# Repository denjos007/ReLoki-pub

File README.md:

# ReLoki-pub

ReLoki  is a Infrastructre-free UWB based relative localization system. It uses a combination of TWR and Geometric AoA for full 3D localizattion and message transfer between participating agents. 

This repository will contain the hardware schematics to get ReLoki operational. 

# Hardware

The files to fabricate the PCB for ReLoki are in hardware folder.
1. ReLoki_ECAD: ReLoki Controller PCB 
2. UWB_Antenna_Circular: Individual circular antenna
3. UWB_Antenna_SqArray: UWB antenna in the uniform circular array configuration
4. 3D Parts: 3D printed parts for the RTA Antenna array.

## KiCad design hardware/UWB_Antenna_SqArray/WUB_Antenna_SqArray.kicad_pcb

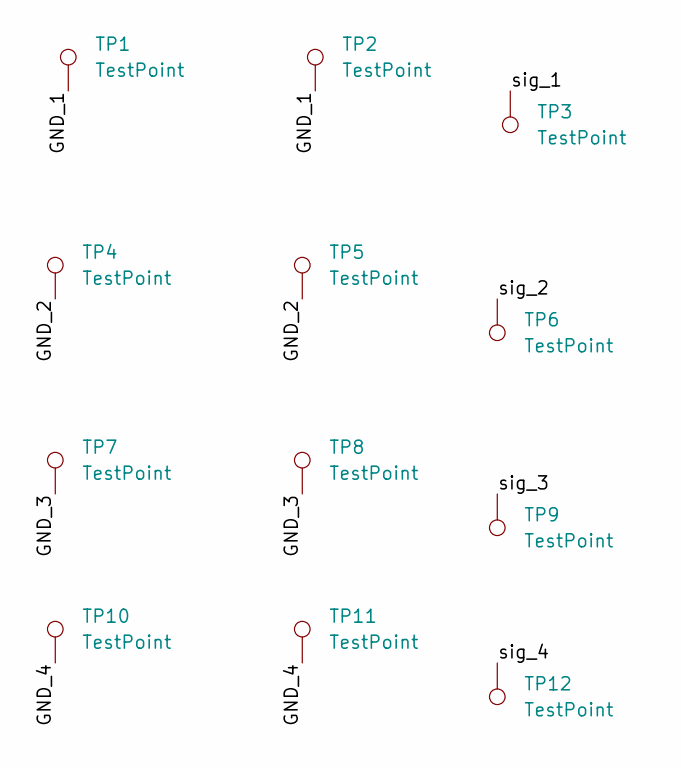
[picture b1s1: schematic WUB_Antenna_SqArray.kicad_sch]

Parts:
TP1, TP2, TP4, TP5, TP7, TP8, TP10, TP11: TestPoint; TestPoint_Pad_2.0x2.0mm
TP3, TP6, TP9, TP12: TestPoint; TestPoint_Pad_1.0x1.0mm

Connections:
/GND_1: TP1.1, TP2.1
/GND_2: TP4.1, TP5.1
/GND_3: TP7.1, TP8.1
/GND_4: TP10.1, TP11.1
/sig_1: TP3.1
/sig_2: TP6.1
/sig_3: TP9.1
/sig_4: TP12.1

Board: 2 copper layers, 16 parts (2 on the bottom side), 4 nets, no tracks yet.

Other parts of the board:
kibuzzard-664B60AC: G***; kibuzzard-664B60AC
kibuzzard-6643D5B9: G***; kibuzzard-6643D5B9
kibuzzard-6643D605: G***; kibuzzard-6643D605
kibuzzard-6643D800: G***; kibuzzard-6643D800

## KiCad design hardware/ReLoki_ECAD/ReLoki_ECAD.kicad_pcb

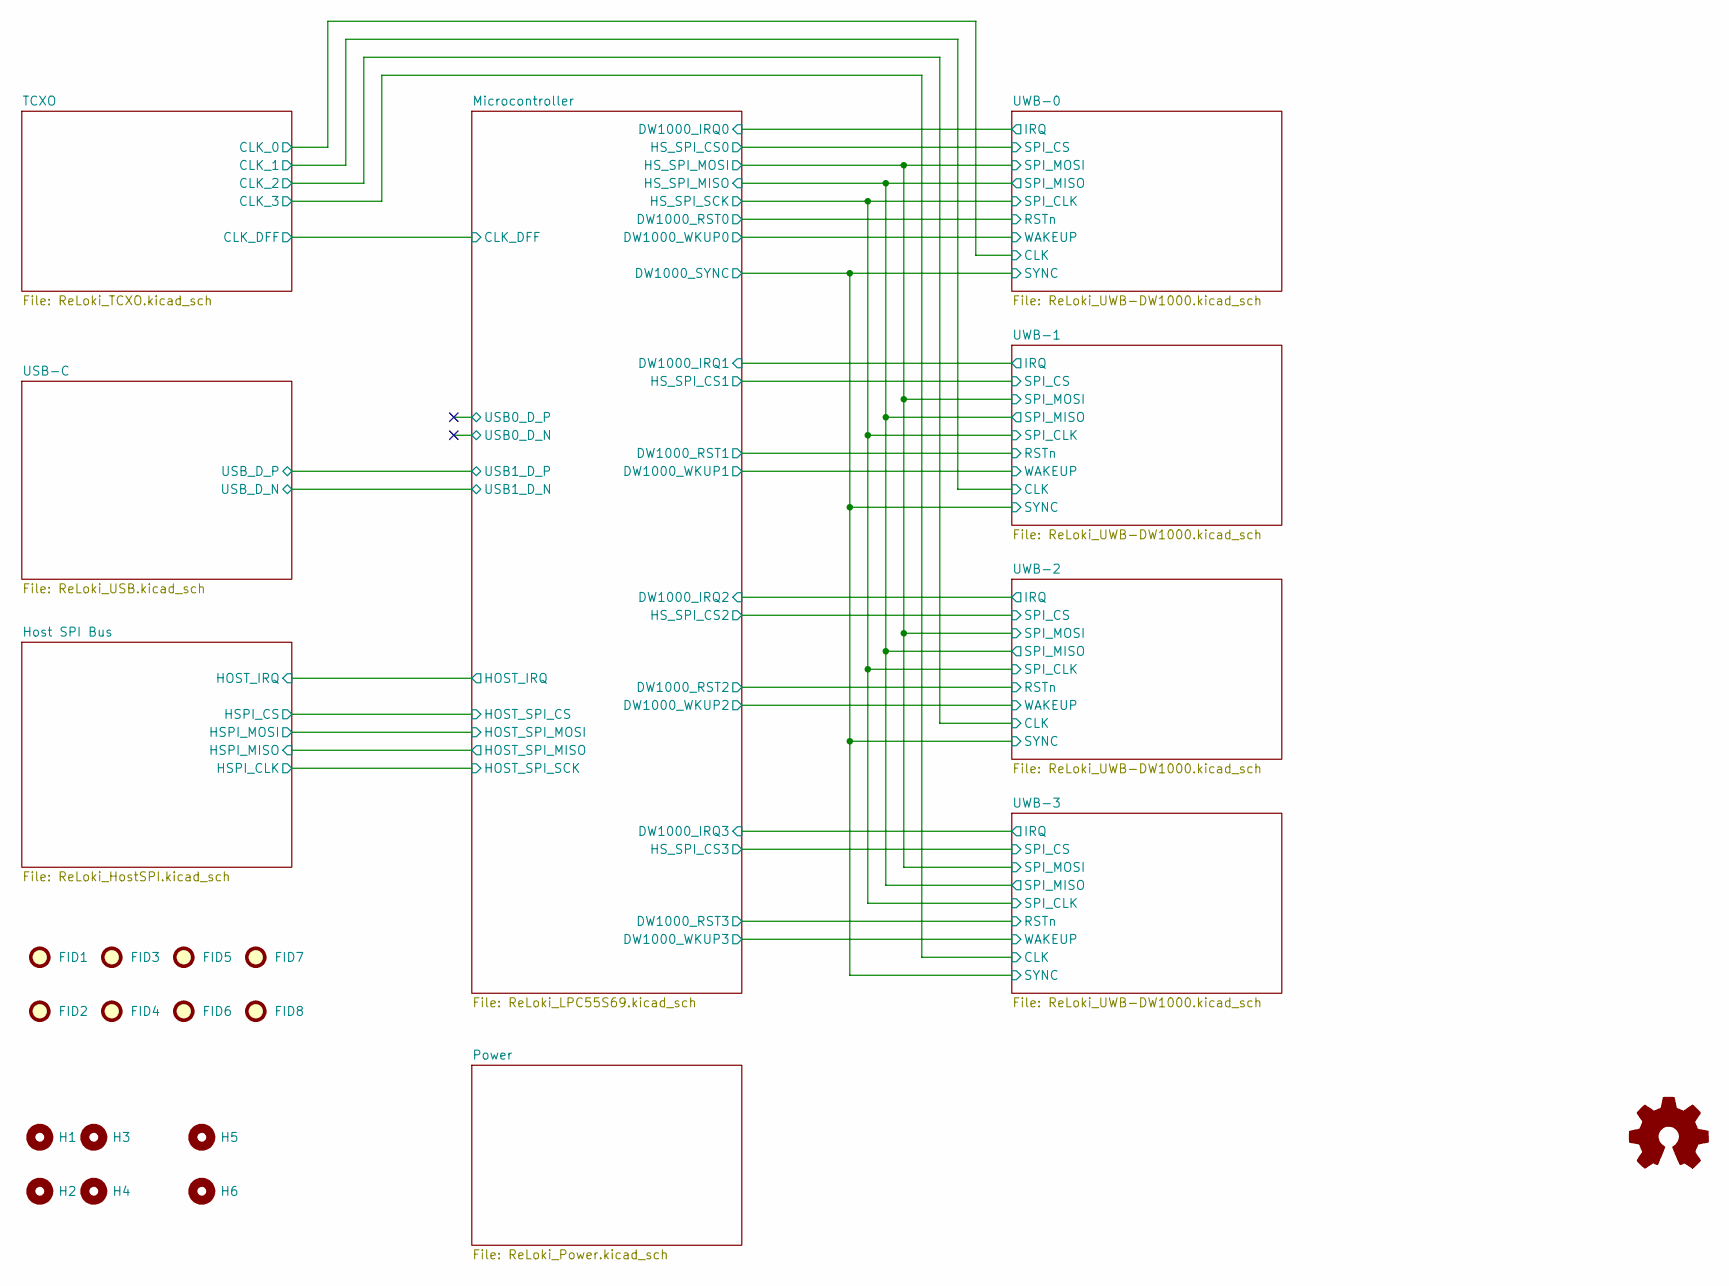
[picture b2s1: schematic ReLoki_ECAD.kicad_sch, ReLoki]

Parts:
FID1, FID2, FID3, FID4, FID5, FID6, FID7, FID8: Fiducial; Fiducial_0.75mm_Mask1.5mm
H1, H2, H3, H4: MountingHole; MountingHole_2.2mm_M2_Pad_Via
H5, H6: MountingHole; MountingHole_2.2mm_M2_Pad

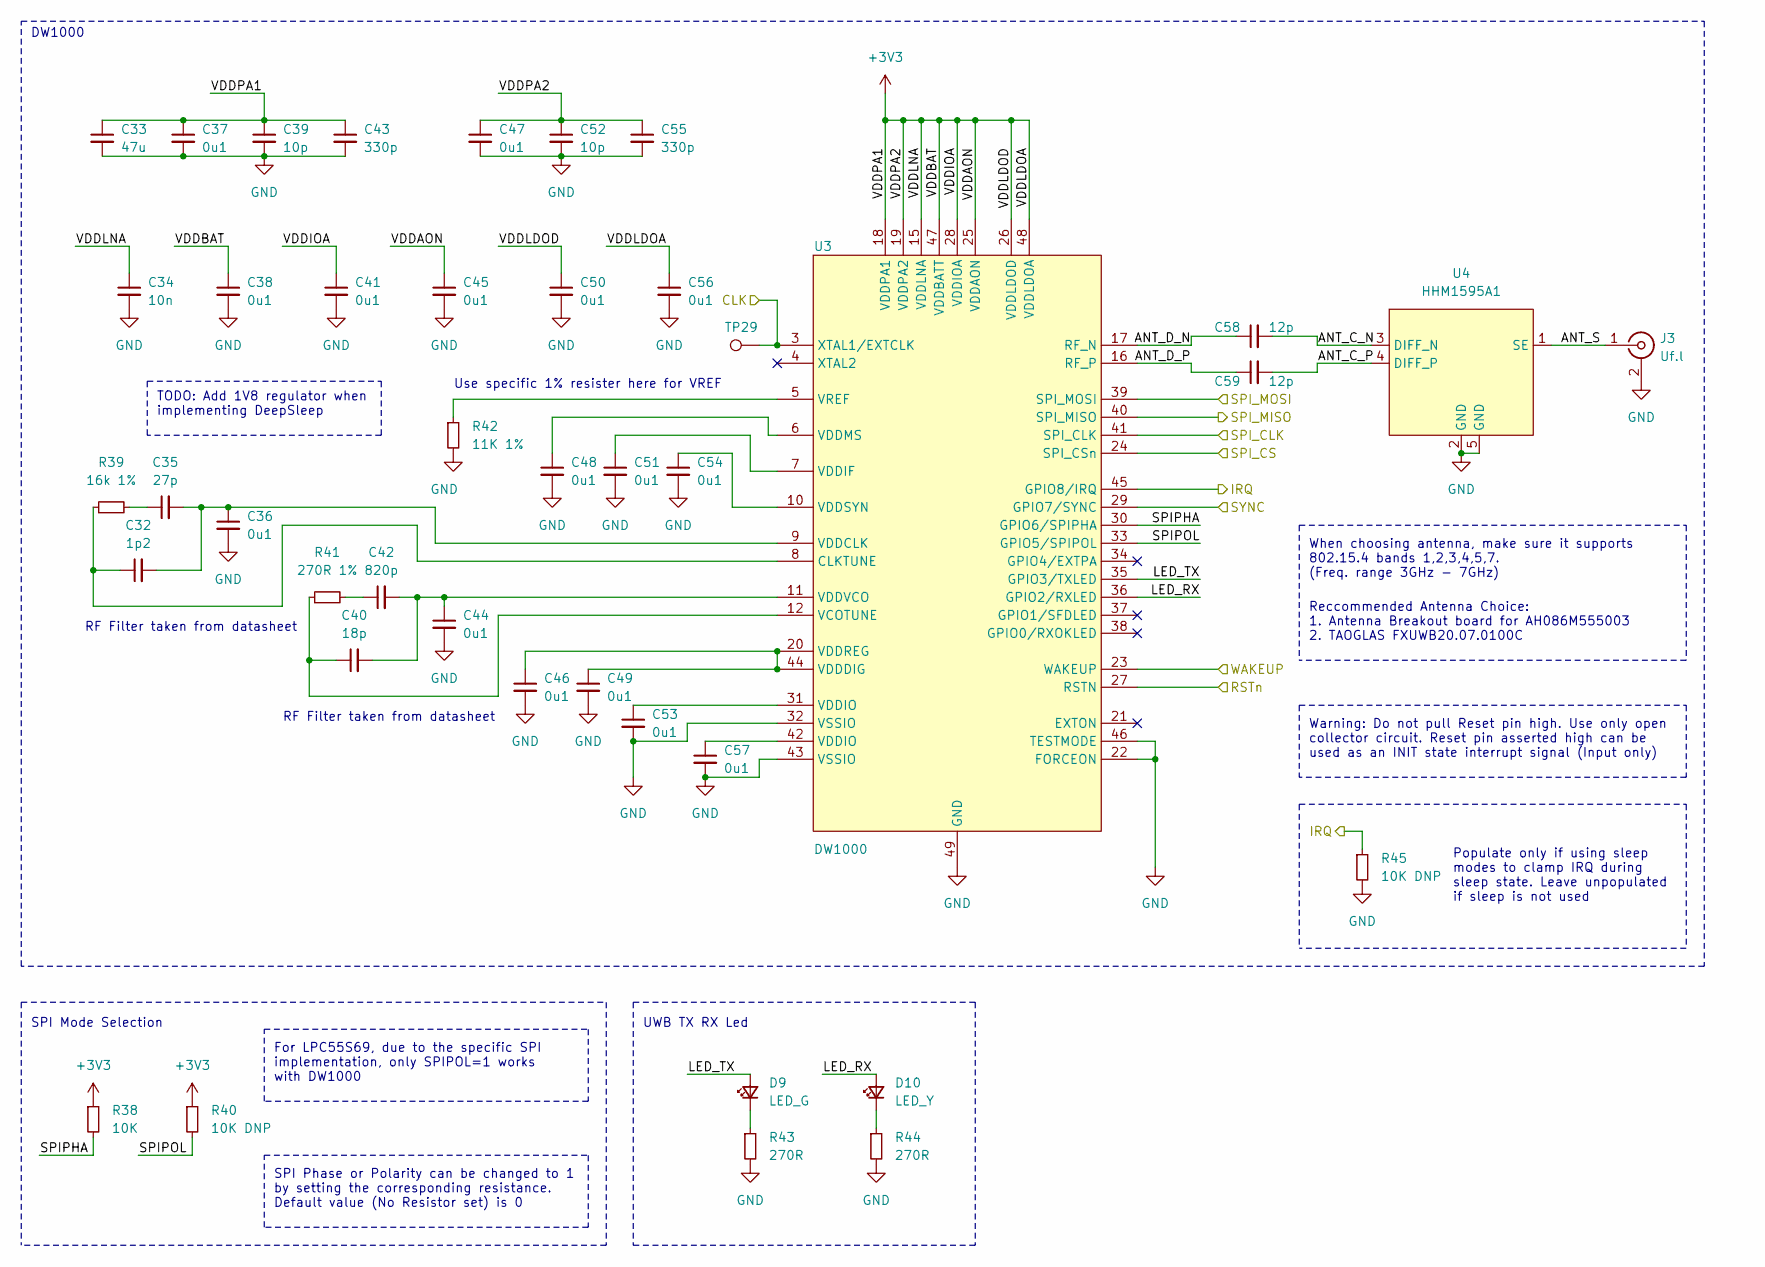
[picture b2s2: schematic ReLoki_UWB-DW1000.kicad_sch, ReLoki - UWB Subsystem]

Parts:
C32: 1p2; C_0402_1005Metric
C33: 47u; C_0603_1608Metric
C34: 10n; C_0402_1005Metric
C35: 27p; C_0402_1005Metric
C36, C37, C38, C41, C44, C45, C46, C47, C48, C49, C50, C51, C53, C54, C56, C57: 0u1; C_0402_1005Metric
C39, C52: 10p; C_0402_1005Metric
C40: 18p; C_0402_1005Metric
C42: 820p; C_0402_1005Metric
C43, C55: 330p; C_0402_1005Metric
C58, C59: 12p; C_0402_1005Metric
D9: LED_G; LED_0603_1608Metric
D10: LED_Y; LED_0603_1608Metric
J3: Uf.l; U.FL_Hirose_U.FL-R-SMT-1_Vertical
R38: 10K; R_0402_1005Metric
R39: 16k 1%; R_0402_1005Metric
R40, R45: 10K DNP; R_0402_1005Metric
R41: 270R 1%; R_0402_1005Metric
R42: 11K 1%; R_0402_1005Metric
R43, R44: 270R; R_0402_1005Metric
TP29: TestPoint; TestPoint_Pad_D1.0mm
U3: DW1000; QFN-48-1EP_6x6mm_P0.4mm_EP4.2x4.2mm_ThermalVias
U4: HHM1595A1

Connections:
+3V3: C33.1, C34.1, C37.1, C38.1, C39.1, C41.1, C43.1, C45.1, C47.1, C50.1, C52.1, C55.1, C56.1, R38.1, R40.1, U3.15 (VDDLNA), U3.18 (VDDPA1), U3.19 (VDDPA2), U3.25 (VDDAON), U3.26 (VDDLDOD), U3.28 (VDDIOA), U3.47 (VDDBATT), U3.48 (VDDLDOA); also elsewhere on the board
/Microcontroller/DW1000_IRQ0: R45.1, U3.45 (GPIO8/IRQ); also elsewhere on the board
/Microcontroller/DW1000_RST0: U3.27 (RSTN); also elsewhere on the board
/Microcontroller/DW1000_SYNC: U3.29 (GPIO7/SYNC); also elsewhere on the board
/Microcontroller/DW1000_WKUP0: U3.23 (WAKEUP); also elsewhere on the board
/Microcontroller/HS_SPI_CS0: U3.24 (SPI_CSn); also elsewhere on the board
/Microcontroller/HS_SPI_MISO: U3.40 (SPI_MISO); also elsewhere on the board
/Microcontroller/HS_SPI_MOSI: U3.39 (SPI_MOSI); also elsewhere on the board
/Microcontroller/HS_SPI_SCK: U3.41 (SPI_CLK); also elsewhere on the board
/TCXO/CLK_0: TP29.1, U3.3 (XTAL1/EXTCLK); also elsewhere on the board
/UWB-0/ANT_C_N: C58.2, U4.3 (DIFF_N)
/UWB-0/ANT_C_P: C59.2, U4.4 (DIFF_P)
/UWB-0/ANT_D_N: C58.1, U3.17 (RF_N)
/UWB-0/ANT_D_P: C59.1, U3.16 (RF_P)
/UWB-0/ANT_S: J3.1 (In), U4.1 (SE)
/UWB-0/LED_RX: D10.2 (A), U3.36 (GPIO2/RXLED)
/UWB-0/LED_TX: D9.2 (A), U3.35 (GPIO3/TXLED)
/UWB-0/SPIPHA: R38.2, U3.30 (GPIO6/SPIPHA)
/UWB-0/SPIPOL: R40.2, U3.33 (GPIO5/SPIPOL)
GND: C33.2, C34.2, C36.2, C37.2, C38.2, C39.2, C41.2, C43.2, C44.2, C45.2, C46.2, C47.2, C48.2, C49.2, C50.2, C51.2, C52.2, C53.2, C54.2, C55.2, C56.2, C57.2, J3.2 (Ext), R42.2, R43.2, R44.2, R45.2, U3.22 (FORCEON), U3.32 (VSSIO), U3.43 (VSSIO), U3.46 (TESTMODE), U3.49 (GND), U4.2 (GND), U4.5 (GND); also elsewhere on the board
unnamed: C32.1, R39.1, U3.8 (CLKTUNE)
unnamed: C32.2, C35.2, C36.1, U3.9 (VDDCLK)
unnamed: C35.1, R39.2
unnamed: C40.1, R41.1, U3.12 (VCOTUNE)
unnamed: C40.2, C42.2, C44.1, U3.11 (VDDVCO)
unnamed: C42.1, R41.2
unnamed: C46.1, C49.1, U3.20 (VDDREG), U3.44 (VDDDIG)
unnamed: C48.1, U3.6 (VDDMS)
unnamed: C51.1, U3.7 (VDDIF)
unnamed: C53.1, U3.31 (VDDIO)
unnamed: C54.1, U3.10 (VDDSYN)
unnamed: C57.1, U3.42 (VDDIO)
unnamed: D9.1 (K), R43.1
unnamed: D10.1 (K), R44.1
unnamed: R42.1, U3.5 (VREF)

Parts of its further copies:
C60, C88, C116: 1p2; C_0402_1005Metric
C61, C89, C117: 47u; C_0603_1608Metric
C62, C90, C118: 10n; C_0402_1005Metric
C63, C91, C119: 27p; C_0402_1005Metric
C64, C65, C66, C69, C72, C73, C74, C75, C76, C77, C78, C79, C81, C82, C84, C85, C92, C93, C94, C97, C100, C101, C102, C103, C104, C105, C106, C107, C109, C110, C112, C113, C120, C121, C122, C125, C128, C129, C130, C131, C132, C133, C134, C135, C137, C138, C140, C141: 0u1; C_0402_1005Metric
C67, C80, C95, C108, C123, C136: 10p; C_0402_1005Metric
C68, C96, C124: 18p; C_0402_1005Metric
C70, C98, C126: 820p; C_0402_1005Metric
C71, C83, C99, C111, C127, C139: 330p; C_0402_1005Metric
C86, C87, C114, C115, C142, C143: 12p; C_0402_1005Metric
D11, D13, D15: LED_G; LED_0603_1608Metric
D12, D14, D16: LED_Y; LED_0603_1608Metric
J4, J5, J6: Uf.l; U.FL_Hirose_U.FL-R-SMT-1_Vertical
R46, R54, R62: 10K; R_0402_1005Metric
R47, R55, R63: 16k 1%; R_0402_1005Metric
R48, R53, R56, R61, R64, R69: 10K DNP; R_0402_1005Metric
R49, R57, R65: 270R 1%; R_0402_1005Metric
R50, R58, R66: 11K 1%; R_0402_1005Metric
R51, R52, R59, R60, R67, R68: 270R; R_0402_1005Metric
TP30, TP31, TP32: TestPoint; TestPoint_Pad_D1.0mm
U5, U7, U9: DW1000; QFN-48-1EP_6x6mm_P0.4mm_EP4.2x4.2mm_ThermalVias
U6, U8, U10: HHM1595A1

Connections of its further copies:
+3V3: C61.1, C62.1, C65.1, C66.1, C67.1, C69.1, C71.1, C73.1, C75.1, C78.1, C80.1, C83.1, C84.1, C89.1, C90.1, C93.1, C94.1, C95.1, C97.1, C99.1, C101.1, C103.1, C106.1, C108.1, C111.1, C112.1, C117.1, C118.1, C121.1, C122.1, C123.1, C125.1, C127.1, C129.1, C131.1, C134.1, C136.1, C139.1, C140.1, R46.1, R48.1, R54.1, R56.1, R62.1, R64.1, U5.15 (VDDLNA), U5.18 (VDDPA1), U5.19 (VDDPA2), U5.25 (VDDAON), U5.26 (VDDLDOD), U5.28 (VDDIOA), U5.47 (VDDBATT), U5.48 (VDDLDOA), U7.15 (VDDLNA), U7.18 (VDDPA1), U7.19 (VDDPA2), U7.25 (VDDAON), U7.26 (VDDLDOD), U7.28 (VDDIOA), U7.47 (VDDBATT), U7.48 (VDDLDOA), U9.15 (VDDLNA), U9.18 (VDDPA1), U9.19 (VDDPA2), U9.25 (VDDAON), U9.26 (VDDLDOD), U9.28 (VDDIOA), U9.47 (VDDBATT), U9.48 (VDDLDOA); also elsewhere on the board
/Microcontroller/DW1000_IRQ1: R53.1, U5.45 (GPIO8/IRQ); also elsewhere on the board
/Microcontroller/DW1000_IRQ2: R61.1, U7.45 (GPIO8/IRQ); also elsewhere on the board
/Microcontroller/DW1000_IRQ3: R69.1, U9.45 (GPIO8/IRQ); also elsewhere on the board
/Microcontroller/DW1000_RST1: U5.27 (RSTN); also elsewhere on the board
/Microcontroller/DW1000_RST2: U7.27 (RSTN); also elsewhere on the board
/Microcontroller/DW1000_RST3: U9.27 (RSTN); also elsewhere on the board
/Microcontroller/DW1000_SYNC: U5.29 (GPIO7/SYNC), U7.29 (GPIO7/SYNC), U9.29 (GPIO7/SYNC); also elsewhere on the board
/Microcontroller/DW1000_WKUP1: U5.23 (WAKEUP); also elsewhere on the board
/Microcontroller/DW1000_WKUP2: U7.23 (WAKEUP); also elsewhere on the board
/Microcontroller/DW1000_WKUP3: U9.23 (WAKEUP); also elsewhere on the board
/Microcontroller/HS_SPI_CS1: U5.24 (SPI_CSn); also elsewhere on the board
/Microcontroller/HS_SPI_CS2: U7.24 (SPI_CSn); also elsewhere on the board
/Microcontroller/HS_SPI_CS3: U9.24 (SPI_CSn); also elsewhere on the board
/Microcontroller/HS_SPI_MISO: U5.40 (SPI_MISO), U7.40 (SPI_MISO), U9.40 (SPI_MISO); also elsewhere on the board
/Microcontroller/HS_SPI_MOSI: U5.39 (SPI_MOSI), U7.39 (SPI_MOSI), U9.39 (SPI_MOSI); also elsewhere on the board
/Microcontroller/HS_SPI_SCK: U5.41 (SPI_CLK), U7.41 (SPI_CLK), U9.41 (SPI_CLK); also elsewhere on the board
/TCXO/CLK_1: TP30.1, U5.3 (XTAL1/EXTCLK); also elsewhere on the board
/TCXO/CLK_2: TP31.1, U7.3 (XTAL1/EXTCLK); also elsewhere on the board
/TCXO/CLK_3: TP32.1, U9.3 (XTAL1/EXTCLK); also elsewhere on the board
/UWB-1/ANT_C_N: C86.2, U6.3 (DIFF_N)
/UWB-1/ANT_C_P: C87.2, U6.4 (DIFF_P)
/UWB-1/ANT_D_N: C86.1, U5.17 (RF_N)
/UWB-1/ANT_D_P: C87.1, U5.16 (RF_P)
/UWB-1/ANT_S: J4.1 (In), U6.1 (SE)
/UWB-1/LED_RX: D12.2 (A), U5.36 (GPIO2/RXLED)
/UWB-1/LED_TX: D11.2 (A), U5.35 (GPIO3/TXLED)
/UWB-1/SPIPHA: R46.2, U5.30 (GPIO6/SPIPHA)
/UWB-1/SPIPOL: R48.2, U5.33 (GPIO5/SPIPOL)
/UWB-2/ANT_C_N: C114.2, U8.3 (DIFF_N)
/UWB-2/ANT_C_P: C115.2, U8.4 (DIFF_P)
/UWB-2/ANT_D_N: C114.1, U7.17 (RF_N)
/UWB-2/ANT_D_P: C115.1, U7.16 (RF_P)
/UWB-2/ANT_S: J5.1 (In), U8.1 (SE)
/UWB-2/LED_RX: D14.2 (A), U7.36 (GPIO2/RXLED)
/UWB-2/LED_TX: D13.2 (A), U7.35 (GPIO3/TXLED)
/UWB-2/SPIPHA: R54.2, U7.30 (GPIO6/SPIPHA)
/UWB-2/SPIPOL: R56.2, U7.33 (GPIO5/SPIPOL)
/UWB-3/ANT_C_N: C142.2, U10.3 (DIFF_N)
/UWB-3/ANT_C_P: C143.2, U10.4 (DIFF_P)
/UWB-3/ANT_D_N: C142.1, U9.17 (RF_N)
/UWB-3/ANT_D_P: C143.1, U9.16 (RF_P)
/UWB-3/ANT_S: J6.1 (In), U10.1 (SE)
/UWB-3/LED_RX: D16.2 (A), U9.36 (GPIO2/RXLED)
/UWB-3/LED_TX: D15.2 (A), U9.35 (GPIO3/TXLED)
/UWB-3/SPIPHA: R62.2, U9.30 (GPIO6/SPIPHA)
/UWB-3/SPIPOL: R64.2, U9.33 (GPIO5/SPIPOL)
GND: C61.2, C62.2, C64.2, C65.2, C66.2, C67.2, C69.2, C71.2, C72.2, C73.2, C74.2, C75.2, C76.2, C77.2, C78.2, C79.2, C80.2, C81.2, C82.2, C83.2, C84.2, C85.2, C89.2, C90.2, C92.2, C93.2, C94.2, C95.2, C97.2, C99.2, C100.2, C101.2, C102.2, C103.2, C104.2, C105.2, C106.2, C107.2, C108.2, C109.2, C110.2, C111.2, C112.2, C113.2, C117.2, C118.2, C120.2, C121.2, C122.2, C123.2, C125.2, C127.2, C128.2, C129.2, C130.2, C131.2, C132.2, C133.2, C134.2, C135.2, C136.2, C137.2, C138.2, C139.2, C140.2, C141.2, J4.2 (Ext), J5.2 (Ext), J6.2 (Ext), R50.2, R51.2, R52.2, R53.2, R58.2, R59.2, R60.2, R61.2, R66.2, R67.2, R68.2, R69.2, U5.22 (FORCEON), U5.32 (VSSIO), U5.43 (VSSIO), U5.46 (TESTMODE), U5.49 (GND), U6.2 (GND), U6.5 (GND), U7.22 (FORCEON), U7.32 (VSSIO), U7.43 (VSSIO), U7.46 (TESTMODE), U7.49 (GND), U8.2 (GND), U8.5 (GND), U9.22 (FORCEON), U9.32 (VSSIO), U9.43 (VSSIO), U9.46 (TESTMODE), U9.49 (GND), U10.2 (GND), U10.5 (GND); also elsewhere on the board
unnamed: C60.1, R47.1, U5.8 (CLKTUNE)
unnamed: C60.2, C63.2, C64.1, U5.9 (VDDCLK)
unnamed: C63.1, R47.2
unnamed: C68.1, R49.1, U5.12 (VCOTUNE)
unnamed: C68.2, C70.2, C72.1, U5.11 (VDDVCO)
unnamed: C70.1, R49.2
unnamed: C74.1, C77.1, U5.20 (VDDREG), U5.44 (VDDDIG)
unnamed: C76.1, U5.6 (VDDMS)
unnamed: C79.1, U5.7 (VDDIF)
unnamed: C81.1, U5.31 (VDDIO)
unnamed: C82.1, U5.10 (VDDSYN)
unnamed: C85.1, U5.42 (VDDIO)
unnamed: C88.1, R55.1, U7.8 (CLKTUNE)
unnamed: C88.2, C91.2, C92.1, U7.9 (VDDCLK)
unnamed: C91.1, R55.2
unnamed: C96.1, R57.1, U7.12 (VCOTUNE)
unnamed: C98.1, R57.2
unnamed: C96.2, C98.2, C100.1, U7.11 (VDDVCO)
unnamed: C102.1, C105.1, U7.20 (VDDREG), U7.44 (VDDDIG)
unnamed: C104.1, U7.6 (VDDMS)
unnamed: C107.1, U7.7 (VDDIF)
unnamed: C109.1, U7.31 (VDDIO)
unnamed: C110.1, U7.10 (VDDSYN)
unnamed: C113.1, U7.42 (VDDIO)
unnamed: C116.1, R63.1, U9.8 (CLKTUNE)
unnamed: C116.2, C119.2, C120.1, U9.9 (VDDCLK)
unnamed: C119.1, R63.2
unnamed: C124.1, R65.1, U9.12 (VCOTUNE)
unnamed: C124.2, C126.2, C128.1, U9.11 (VDDVCO)
unnamed: C126.1, R65.2
unnamed: C130.1, C133.1, U9.20 (VDDREG), U9.44 (VDDDIG)
unnamed: C132.1, U9.6 (VDDMS)
unnamed: C135.1, U9.7 (VDDIF)
unnamed: C137.1, U9.31 (VDDIO)
unnamed: C138.1, U9.10 (VDDSYN)
unnamed: C141.1, U9.42 (VDDIO)
unnamed: D11.1 (K), R51.1
unnamed: D12.1 (K), R52.1
unnamed: D13.1 (K), R59.1
unnamed: D14.1 (K), R60.1
unnamed: D15.1 (K), R67.1
unnamed: D16.1 (K), R68.1
unnamed: R50.1, U5.5 (VREF)
unnamed: R58.1, U7.5 (VREF)
unnamed: R66.1, U9.5 (VREF)

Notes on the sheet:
Use specific 1% resister here for VREF
RF Filter taken from datasheet
DW1000
When choosing antenna, make sure it supports 802.15.4 bands 1,2,3,4,5,7. (Freq. range 3GHz - 7GHz)
UWB TX RX Led
Reccommended Antenna Choice: 1. Antenna Breakout board for AH086M555003 2. TAOGLAS FXUWB20.07.0100C
SPI Phase or Polarity can be changed to 1 by setting the corresponding resistance. Default value (No Resistor set) is 0
Populate only if using sleep modes to clamp IRQ during sleep state. Leave unpopulated if sleep is not used
SPI Mode Selection
For LPC55S69, due to the specific SPI implementation, only SPIPOL=1 works with DW1000
Warning: Do not pull Reset pin high. Use only open collector circuit. Reset pin asserted high can be used as an INIT state interrupt signal (Input only)
TODO: Add 1V8 regulator when implementing DeepSleep

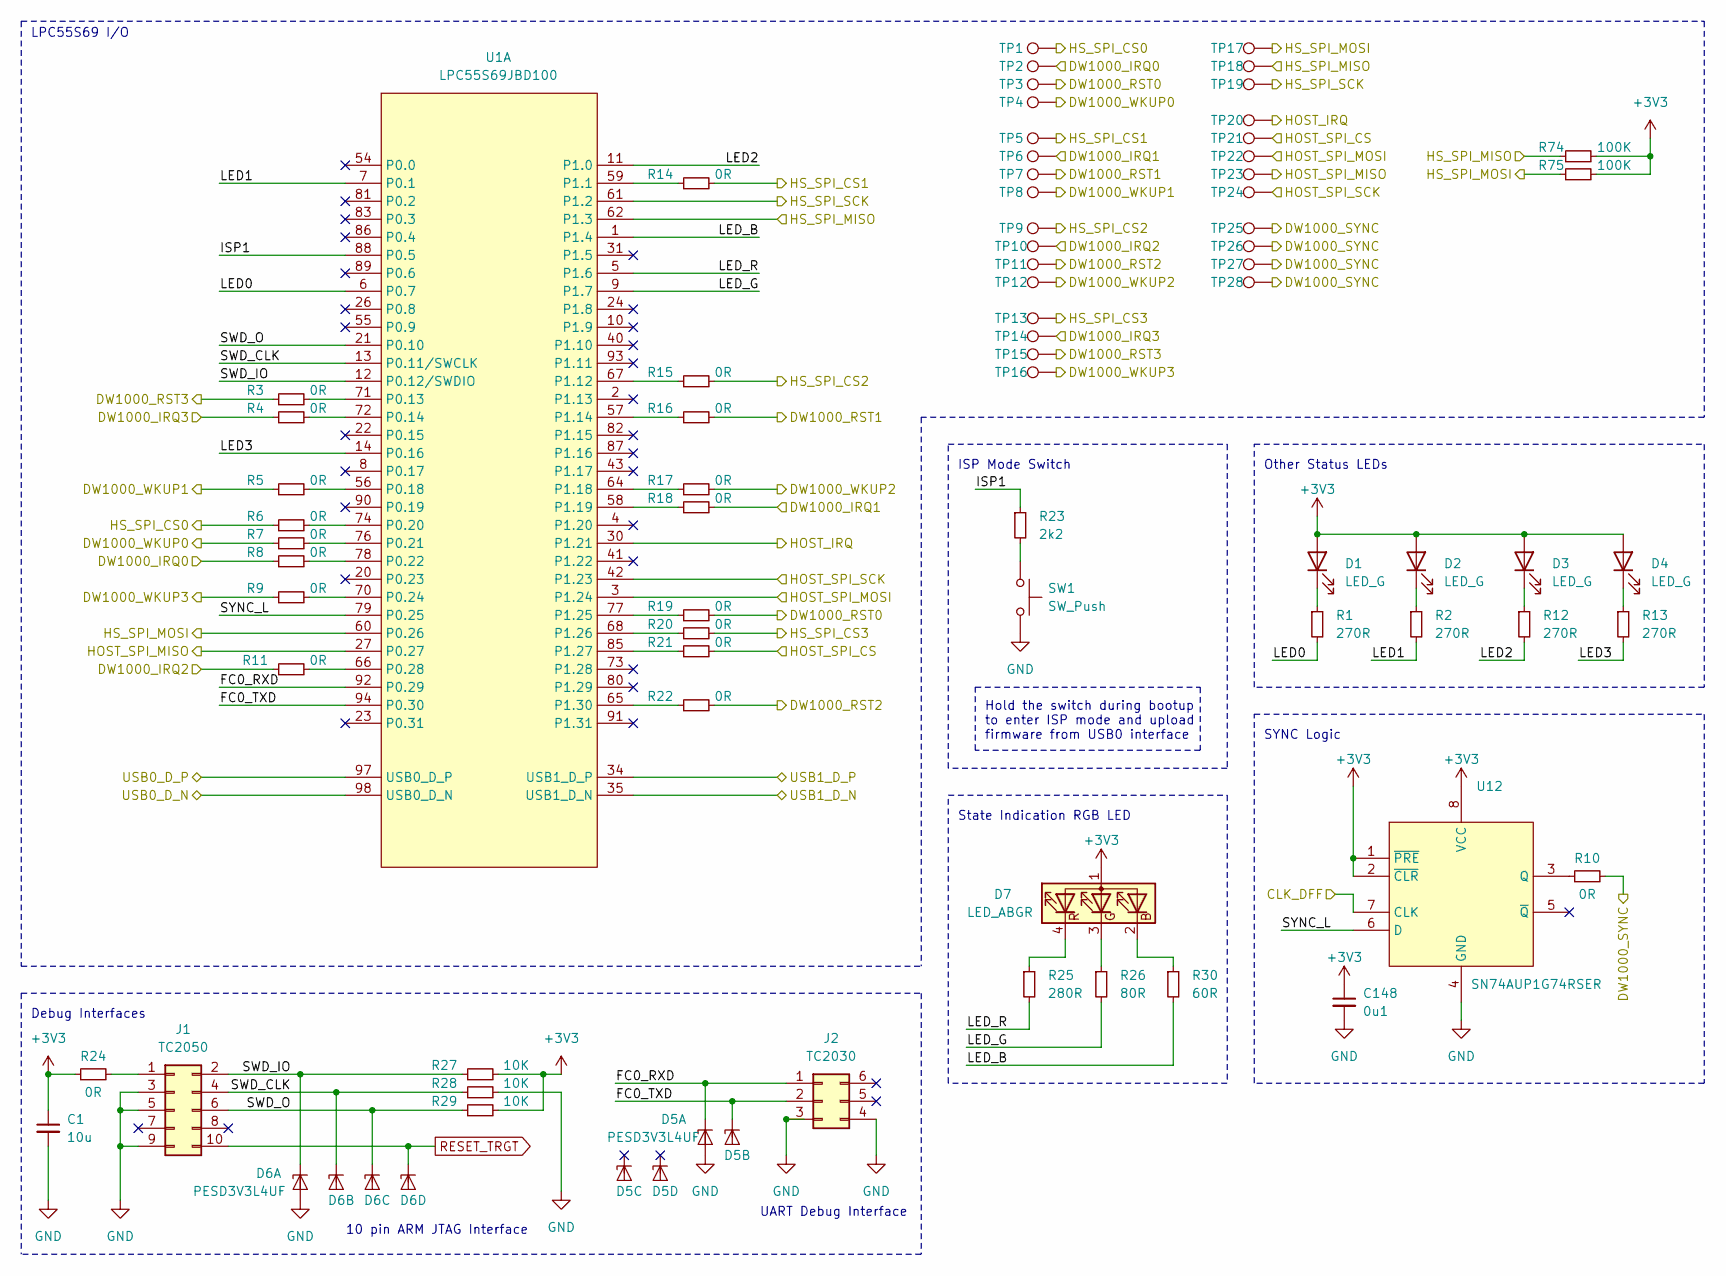
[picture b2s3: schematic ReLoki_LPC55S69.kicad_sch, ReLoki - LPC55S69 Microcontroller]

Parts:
C1: 10u; C_0603_1608Metric
C148: 0u1; C_0402_1005Metric
D1, D2, D3, D4: LED_G; LED_0603_1608Metric
D5, D6: PESD3V3L4UF; SOT-886
D7: LED_ABGR; LED_Cree-PLCC4_2x2mm_CW
J1: TC2050; TC2050-IDC-NL
J2: TC2030; TC2030-IDC-NL
R1, R2, R12, R13: 270R; R_0402_1005Metric
R3, R4, R5, R6, R7, R8, R9, R10, R11, R14, R15, R16, R17, R18, R19, R20, R21, R22, R24: 0R; R_0402_1005Metric
R23: 2k2; R_0402_1005Metric
R25: 280R; R_0402_1005Metric
R26: 80R; R_0402_1005Metric
R27, R28, R29: 10K; R_0402_1005Metric
R30: 60R; R_0402_1005Metric
R74, R75: 100K; R_0402_1005Metric
SW1: SW_Push; Panasonic_EVQPUL_EVQPUC
TP1, TP2, TP3, TP4, TP5, TP6, TP7, TP8, TP9, TP10, TP11, TP12, TP13, TP14, TP15, TP16, TP17, TP18, TP19, TP20, TP21, TP22, TP23, TP24, TP25, TP26, TP27, TP28: TestPoint; TestPoint_Pad_D1.0mm
U1: LPC55S69JBD100; HLQFP-100_14x14mm_P0.5mm
U12: SN74AUP1G74RSER; UQFN-8-1.55x1.55mm_P0.5mm

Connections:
+3V3: C1.1, C148.1, D1.2 (A), D2.2 (A), D3.2 (A), D4.2 (A), D7.1 (A), R24.1, R27.2, R29.2, R74.2, R75.2, U12.1 (~PRE), U12.2 (~CLR), U12.8 (VCC); also elsewhere on the board
/Host SPI Bus/HOST_IRQ: TP20.1, U1.30 (P1.21); also elsewhere on the board
/Host SPI Bus/HSPI_CLK: TP24.1, U1.42 (P1.23); also elsewhere on the board
/Host SPI Bus/HSPI_CS: R21.2, TP21.1; also elsewhere on the board
/Host SPI Bus/HSPI_MISO: TP23.1, U1.27 (P0.27); also elsewhere on the board
/Host SPI Bus/HSPI_MOSI: TP22.1, U1.3 (P1.24); also elsewhere on the board
/Microcontroller/CLK_DFF: U12.7 (CLK); also elsewhere on the board
/Microcontroller/DW1000_IRQ0: R8.1, TP2.1; also elsewhere on the board
/Microcontroller/DW1000_IRQ1: R18.2, TP6.1; also elsewhere on the board
/Microcontroller/DW1000_IRQ2: R11.1, TP10.1; also elsewhere on the board
/Microcontroller/DW1000_IRQ3: R4.1, TP14.1; also elsewhere on the board
/Microcontroller/DW1000_RST0: R19.2, TP3.1; also elsewhere on the board
/Microcontroller/DW1000_RST1: R16.2, TP7.1; also elsewhere on the board
/Microcontroller/DW1000_RST2: R22.2, TP11.1; also elsewhere on the board
/Microcontroller/DW1000_RST3: R3.1, TP15.1; also elsewhere on the board
/Microcontroller/DW1000_SYNC: R10.2, TP25.1, TP26.1, TP27.1, TP28.1; also elsewhere on the board
/Microcontroller/DW1000_WKUP0: R7.1, TP4.1; also elsewhere on the board
/Microcontroller/DW1000_WKUP1: R5.1, TP8.1; also elsewhere on the board
/Microcontroller/DW1000_WKUP2: R17.2, TP12.1; also elsewhere on the board
/Microcontroller/DW1000_WKUP3: R9.1, TP16.1; also elsewhere on the board
/Microcontroller/FC0_RXD: D5.1 (K1), J2.1, U1.92 (P0.29)
/Microcontroller/FC0_TXD: D5.3 (K2), J2.2, U1.94 (P0.30)
/Microcontroller/HS_SPI_CS0: R6.1, TP1.1; also elsewhere on the board
/Microcontroller/HS_SPI_CS1: R14.2, TP5.1; also elsewhere on the board
/Microcontroller/HS_SPI_CS2: R15.2, TP9.1; also elsewhere on the board
/Microcontroller/HS_SPI_CS3: R20.2, TP13.1; also elsewhere on the board
/Microcontroller/HS_SPI_MISO: R74.1, TP18.1, U1.62 (P1.3); also elsewhere on the board
/Microcontroller/HS_SPI_MOSI: R75.1, TP17.1, U1.60 (P0.26); also elsewhere on the board
/Microcontroller/HS_SPI_SCK: TP19.1, U1.61 (P1.2); also elsewhere on the board
/Microcontroller/ISP1: R23.1, U1.88 (P0.5)
/Microcontroller/LED0: R1.2, U1.6 (P0.7)
/Microcontroller/LED1: R2.2, U1.7 (P0.1)
/Microcontroller/LED2: R12.2, U1.11 (P1.0)
/Microcontroller/LED3: R13.2, U1.14 (P0.16)
/Microcontroller/LED_B: R30.2, U1.1 (P1.4)
/Microcontroller/LED_G: R26.2, U1.9 (P1.7)
/Microcontroller/LED_R: R25.2, U1.5 (P1.6)
/Microcontroller/SWD_CLK: D6.3 (K2), J1.4, R28.1, U1.13 (P0.11/SWCLK)
/Microcontroller/SWD_IO: D6.1 (K1), J1.2, R27.1, U1.12 (P0.12/SWDIO)
/Microcontroller/SWD_O: D6.4 (K3), J1.6, R29.1, U1.21 (P0.10)
/Microcontroller/SYNC_L: U1.79 (P0.25), U12.6 (D)
/Microcontroller/USB0_D_N: U1.98 (USB0_D_N)
/Microcontroller/USB0_D_P: U1.97 (USB0_D_P)
/Microcontroller/USB1_D_N: U1.35 (USB1_D_N); also elsewhere on the board
/Microcontroller/USB1_D_P: U1.34 (USB1_D_P); also elsewhere on the board
GND: C1.2, C148.2, D5.2 (A), D5.5 (A), D6.2 (A), D6.5 (A), J1.3, J1.5, J1.9, J2.3, J2.4, R28.2, SW1.1, U12.4 (GND); also elsewhere on the board
unnamed: D1.1 (K), R1.1
unnamed: D2.1 (K), R2.1
unnamed: D3.1 (K), R12.1
unnamed: D4.1 (K), R13.1
unnamed: D7.2 (BK), R30.1
unnamed: D7.3 (GK), R26.1
unnamed: D7.4 (RK), R25.1
unnamed: J1.1, R24.2
unnamed: R3.2, U1.71 (P0.13)
unnamed: R4.2, U1.72 (P0.14)
unnamed: R5.2, U1.56 (P0.18)
unnamed: R6.2, U1.74 (P0.20)
unnamed: R7.2, U1.76 (P0.21)
unnamed: R8.2, U1.78 (P0.22)
unnamed: R9.2, U1.70 (P0.24)
unnamed: R10.1, U12.3 (Q)
unnamed: R11.2, U1.66 (P0.28)
unnamed: R14.1, U1.59 (P1.1)
unnamed: R15.1, U1.67 (P1.12)
unnamed: R16.1, U1.57 (P1.14)
unnamed: R17.1, U1.64 (P1.18)
unnamed: R18.1, U1.58 (P1.19)
unnamed: R19.1, U1.77 (P1.25)
unnamed: R20.1, U1.68 (P1.26)
unnamed: R21.1, U1.85 (P1.27)
unnamed: R22.1, U1.65 (P1.30)
unnamed: R23.2, SW1.2
RESET_TRGT: D6.6 (K4), J1.10; also elsewhere on the board

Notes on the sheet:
Other Status LEDs
10 pin ARM JTAG Interface
UART Debug Interface
Debug Interfaces
State Indication RGB LED
LPC55S69 I/O
Hold the switch during bootup to enter ISP mode and upload firmware from USB0 interface
SYNC Logic
ISP Mode Switch

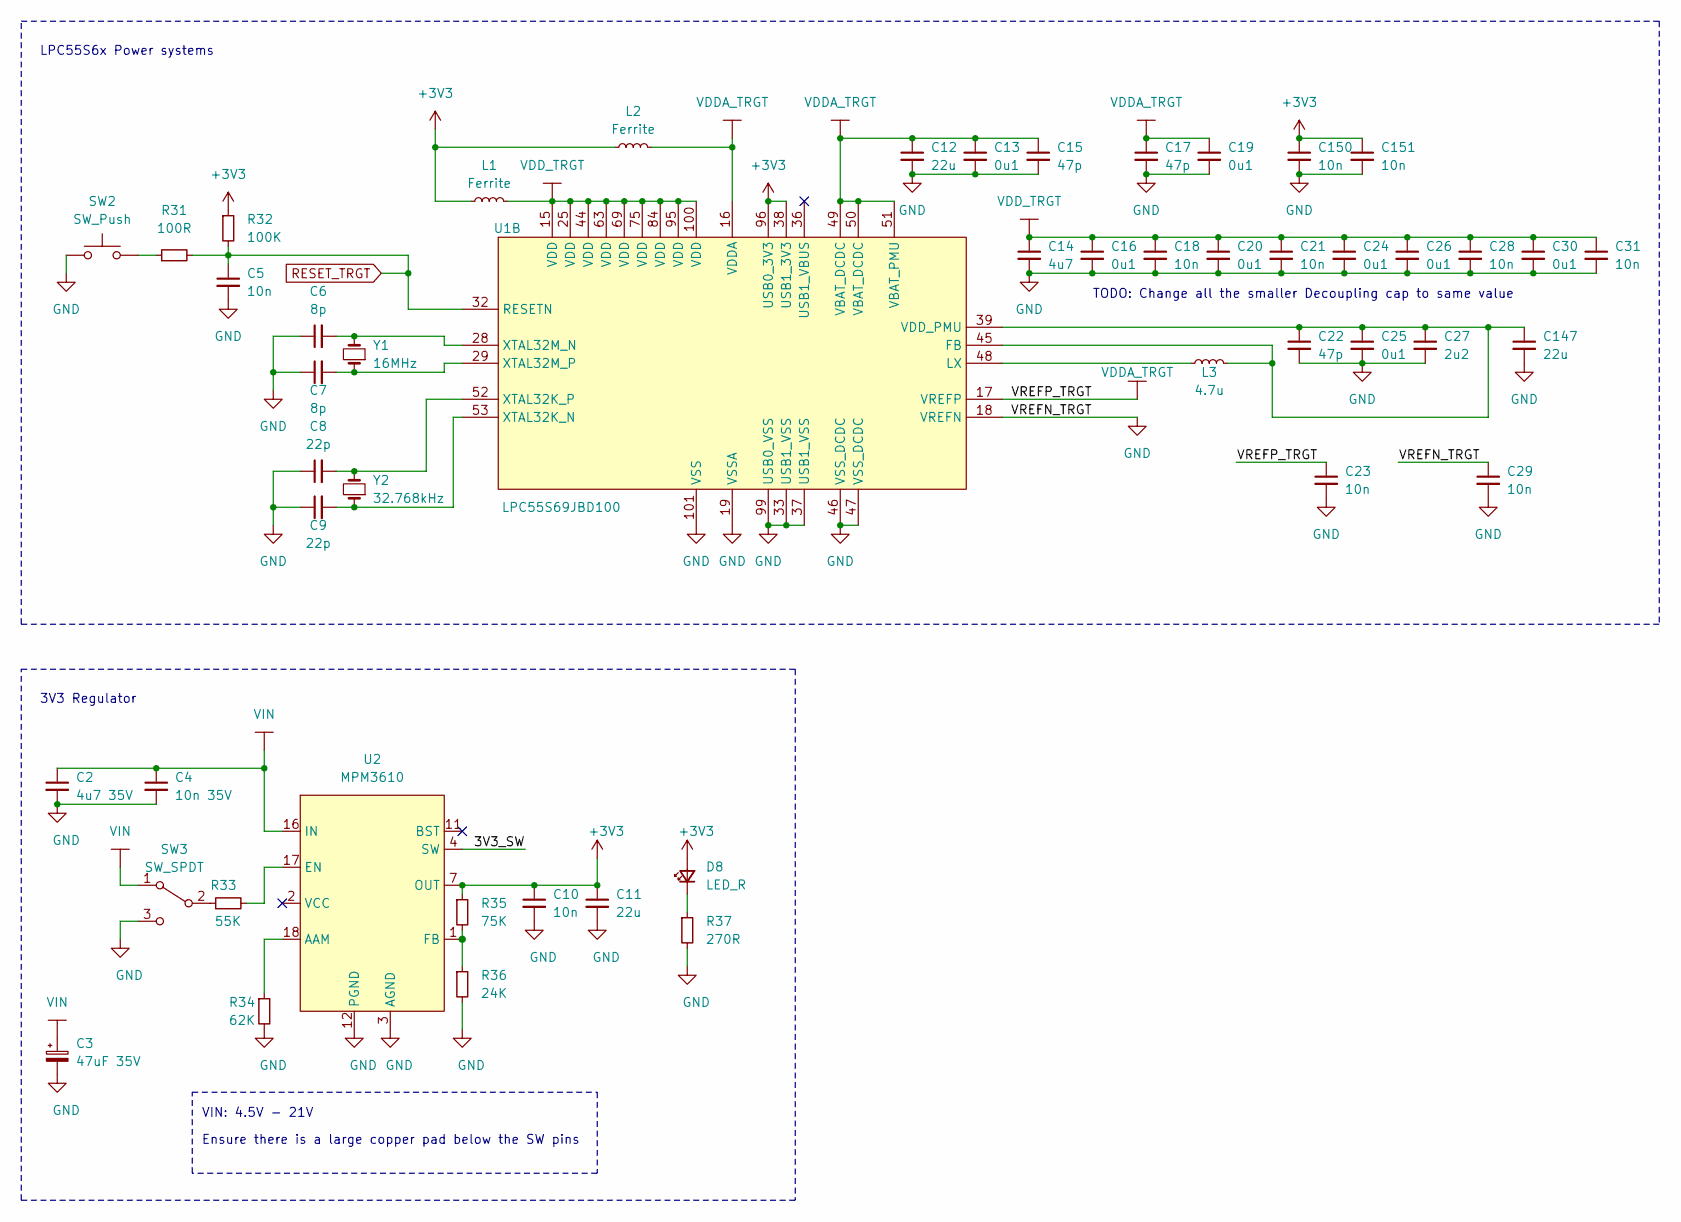
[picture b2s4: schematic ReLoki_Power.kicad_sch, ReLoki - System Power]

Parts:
C2: 4u7 35V; C_0603_1608Metric
C3: 47uF 35V; C_Elec_5x5.8
C4: 10n 35V; C_0402_1005Metric
C5, C10, C18, C21, C23, C28, C29, C31, C150, C151: 10n; C_0402_1005Metric
C6, C7: 8p; C_0402_1005Metric
C8, C9: 22p; C_0402_1005Metric
C11, C12, C147: 22u; C_0603_1608Metric
C13, C16, C19, C20, C24, C25, C26, C30: 0u1; C_0402_1005Metric
C14: 4u7; C_0603_1608Metric
C15, C17, C22: 47p; C_0402_1005Metric
C27: 2u2; C_0603_1608Metric
D8: LED_R; LED_0603_1608Metric
L1, L2: Ferrite; L_0402_1005Metric_Pad0.77x0.64mm_HandSolder
L3: 4.7u; L_0603_1608Metric
R31: 100R; R_0402_1005Metric
R32: 100K; R_0402_1005Metric
R33: 55K; R_0402_1005Metric
R34: 62K; R_0402_1005Metric
R35: 75K; R_0402_1005Metric
R36: 24K; R_0402_1005Metric
R37: 270R; R_0402_1005Metric
SW2: SW_Push; Panasonic_EVQPUL_EVQPUC
SW3: SW_SPDT; SW_SPDT_PCM12
U1: LPC55S69JBD100; HLQFP-100_14x14mm_P0.5mm
U2: MPM3610; MPM3610_QFN-20_5x3mm
Y1: 16MHz; Crystal_SMD_Kyocera_CX3225G-2Pin_3.2x2.5mm
Y2: 32.768kHz; Crystal_SMD_2012-2Pin_2.0x1.2mm

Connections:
+3V3: C10.1, C11.1, C150.1, C151.1, D8.2 (A), L1.1, L2.1, R32.1, R35.1, U1.38 (USB1_3V3), U1.96 (USB0_3V3), U2.7 (OUT), U2.8 (OUT), U2.9 (OUT); also elsewhere on the board
/Power/3V3_SW: U2.4 (SW), U2.5 (SW), U2.6 (SW)
GND: C2.2, C3.2, C4.2, C5.2, C6.1, C7.1, C8.1, C9.1, C10.2, C11.2, C12.2, C13.2, C14.2, C15.2, C16.2, C17.2, C18.2, C19.2, C20.2, C21.2, C22.2, C23.2, C24.2, C25.2, C26.2, C27.2, C28.2, C29.1, C29.2, C30.2, C31.2, C147.2, C150.2, C151.2, R34.2, R36.2, R37.2, SW2.1, SW3.3 (C), U1.18 (VREFN), U1.19 (VSSA), U1.33 (USB1_VSS), U1.37 (USB1_VSS), U1.46 (VSS_DCDC), U1.47 (VSS_DCDC), U1.99 (USB0_VSS), U1.101 (VSS), U2.3 (AGND), U2.12 (PGND), U2.13 (PGND), U2.14 (PGND); also elsewhere on the board
unnamed: C6.2, U1.28 (XTAL32M_N), Y1.2
unnamed: C7.2, U1.29 (XTAL32M_P), Y1.1
unnamed: C8.2, U1.52 (XTAL32K_P), Y2.2
unnamed: C9.2, U1.53 (XTAL32K_N), Y2.1
unnamed: C22.1, C25.1, C27.1, C147.1, L3.2, U1.39 (VDD_PMU), U1.45 (FB)
unnamed: D8.1 (K), R37.1
unnamed: L3.1, U1.48 (LX)
unnamed: R31.1, SW2.2
unnamed: R33.1, SW3.2 (B)
unnamed: R33.2, U2.17 (EN)
unnamed: R34.1, U2.18 (AAM)
unnamed: R35.2, R36.1, U2.1 (FB)
RESET_TRGT: C5.1, R31.2, R32.2, U1.32 (RESETN); also elsewhere on the board
VDDA_TRGT: C12.1, C13.1, C15.1, C17.1, C19.1, C23.1, L2.2, U1.16 (VDDA), U1.17 (VREFP), U1.49 (VBAT_DCDC), U1.50 (VBAT_DCDC), U1.51 (VBAT_PMU)
VDD_TRGT: C14.1, C16.1, C18.1, C20.1, C21.1, C24.1, C26.1, C28.1, C30.1, C31.1, L1.2, U1.15 (VDD), U1.25 (VDD), U1.44 (VDD), U1.63 (VDD), U1.69 (VDD), U1.75 (VDD), U1.84 (VDD), U1.95 (VDD), U1.100 (VDD)
VIN: C2.1, C3.1, C4.1, SW3.1 (A), U2.16 (IN); also elsewhere on the board

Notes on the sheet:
3V3 Regulator
LPC55S6x Power systems
TODO: Change all the smaller Decoupling cap to same value
Ensure there is a large copper pad below the SW pins
VIN: 4.5V - 21V

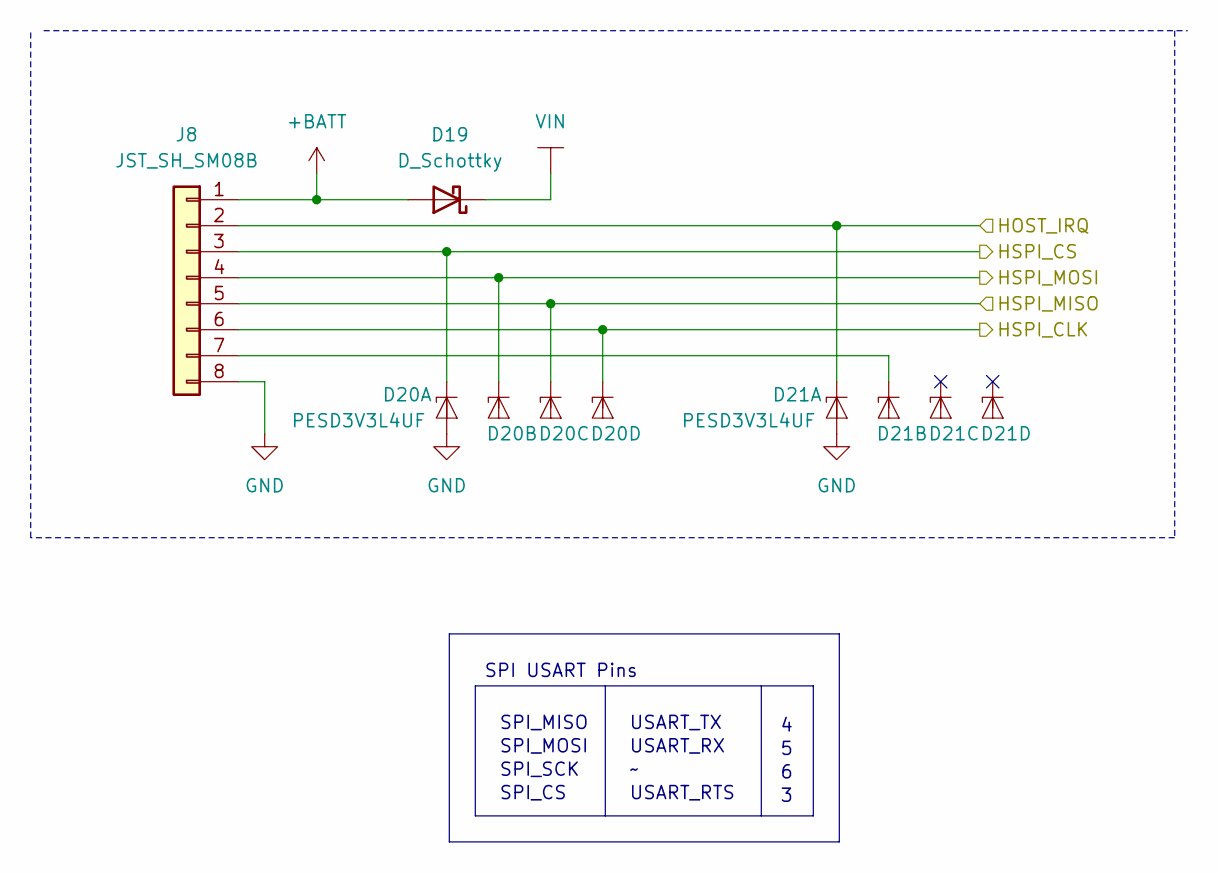
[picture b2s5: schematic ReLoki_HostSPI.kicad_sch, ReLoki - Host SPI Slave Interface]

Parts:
D19: D_Schottky; D_SOD-123F
D20, D21: PESD3V3L4UF; SOT-886
J8: JST_SH_SM08B; JST_SH_SM08B-SRSS-TB_1x08-1MP_P1.00mm_Horizontal

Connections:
+BATT: D19.2 (A), J8.1
/Host SPI Bus/HOST_IRQ: D21.1 (K1), J8.2; also elsewhere on the board
/Host SPI Bus/HSPI_CLK: D20.6 (K4), J8.6; also elsewhere on the board
/Host SPI Bus/HSPI_CS: D20.1 (K1), J8.3; also elsewhere on the board
/Host SPI Bus/HSPI_MISO: D20.4 (K3), J8.5; also elsewhere on the board
/Host SPI Bus/HSPI_MOSI: D20.3 (K2), J8.4; also elsewhere on the board
GND: D20.2 (A), D20.5 (A), D21.2 (A), D21.5 (A), J8.8; also elsewhere on the board
unnamed: D21.3 (K2), J8.7
VIN: D19.1 (K); also elsewhere on the board

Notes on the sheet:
SPI_MOSI
USART_RTS
SPI_SCK
USART_RX
SPI_CS
SPI_MISO
USART_TX
SPI USART Pins
